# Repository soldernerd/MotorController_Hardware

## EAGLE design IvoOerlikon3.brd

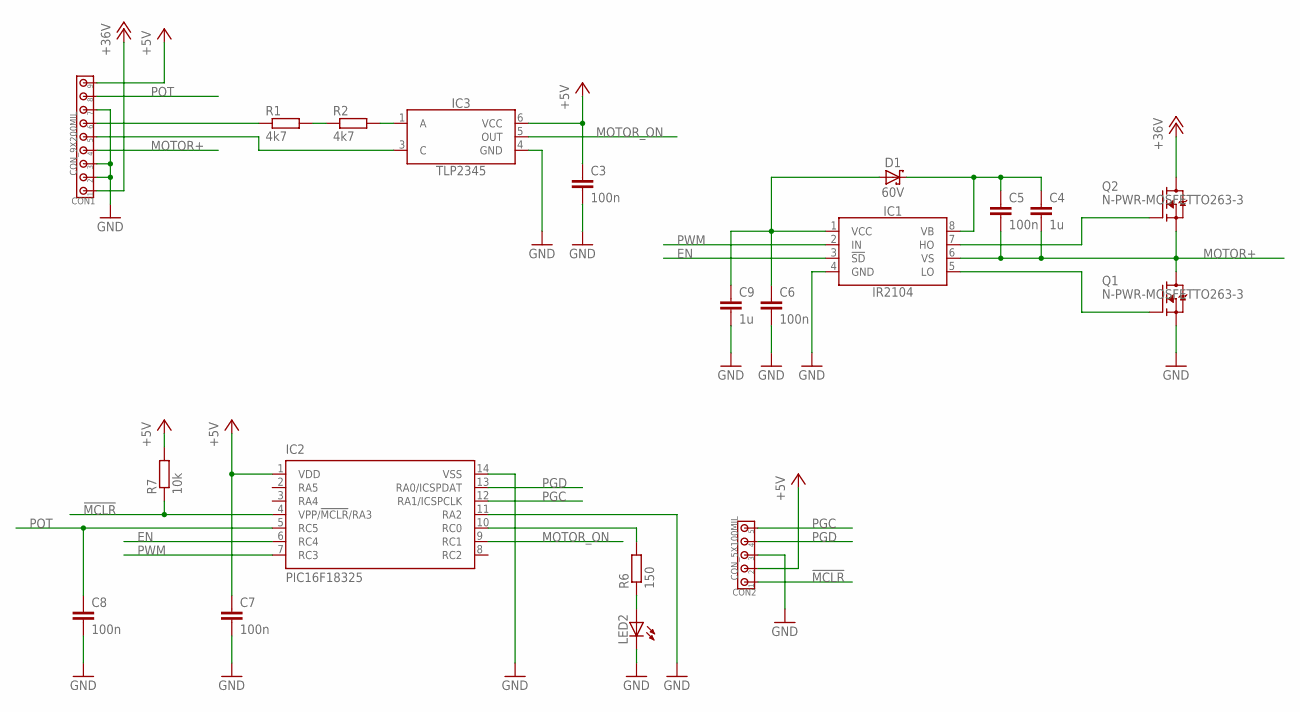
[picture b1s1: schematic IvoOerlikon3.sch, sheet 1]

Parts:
C3, C5, C6, C7, C8: 100n; C0805
C4, C9: 1u; C0805
CON1: CON_9X200MIL; 200MIL_9X
CON2: CON_5X100MIL; 100MIL_5X
D1: 60V; SOD123
IC1: IR2104; SOIC8
IC2: PIC16F18325; SO14
IC3: TLP2345; SO6
LED2: LED0805
Q1, Q2: N-PWR-MOSFETTO263-3; TO263-3
R1, R2: 4k7; R1206
R6: 150; R0805
R7: 10k; R0805

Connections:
!MCLR!: CON2.1, IC2.4 (VPP/!MCLR!/RA3), R7.1
+5V: C3.1, C7.1, CON1.9, CON2.2, IC2.1 (VDD), IC3.6 (VCC), R7.2; also elsewhere on the board
+36V: CON1.1, Q2.TAB (D); also elsewhere on the board
EN: IC1.3 (!SD!), IC2.6 (RC4)
GND: C3.2, C6.2, C7.2, C8.2, C9.2, CON1.2, CON1.3, CON1.7, CON2.3, IC1.4 (GND), IC2.11 (RA2), IC2.14 (VSS), IC3.4 (GND), LED2.C, Q1.3 (S); also elsewhere on the board
MOTOR+: C4.2, C5.2, CON1.4, IC1.6 (VS), Q1.TAB (D), Q2.3 (S)
MOTOR_ON: IC2.9 (RC1), IC3.5 (OUT)
unnamed: R1.2, R2.1
unnamed: IC1.5 (LO), Q1.1 (G)
unnamed: IC3.1 (A), R2.2
unnamed: IC1.7 (HO), Q2.1 (G)
unnamed: C4.1, C5.1, D1.C, IC1.8 (VB)
unnamed: LED2.A, R6.1
unnamed: IC2.10 (RC0), R6.2
unnamed: CON1.6, R1.1
unnamed: CON1.5, IC3.3 (C)
unnamed: C6.1, C9.1, D1.A, IC1.1 (VCC)
PGC: CON2.5, IC2.12 (RA1/ICSPCLK)
PGD: CON2.4, IC2.13 (RA0/ICSPDAT)
POT: C8.1, CON1.8, IC2.5 (RC5)
PWM: IC1.2 (IN), IC2.7 (RC3)

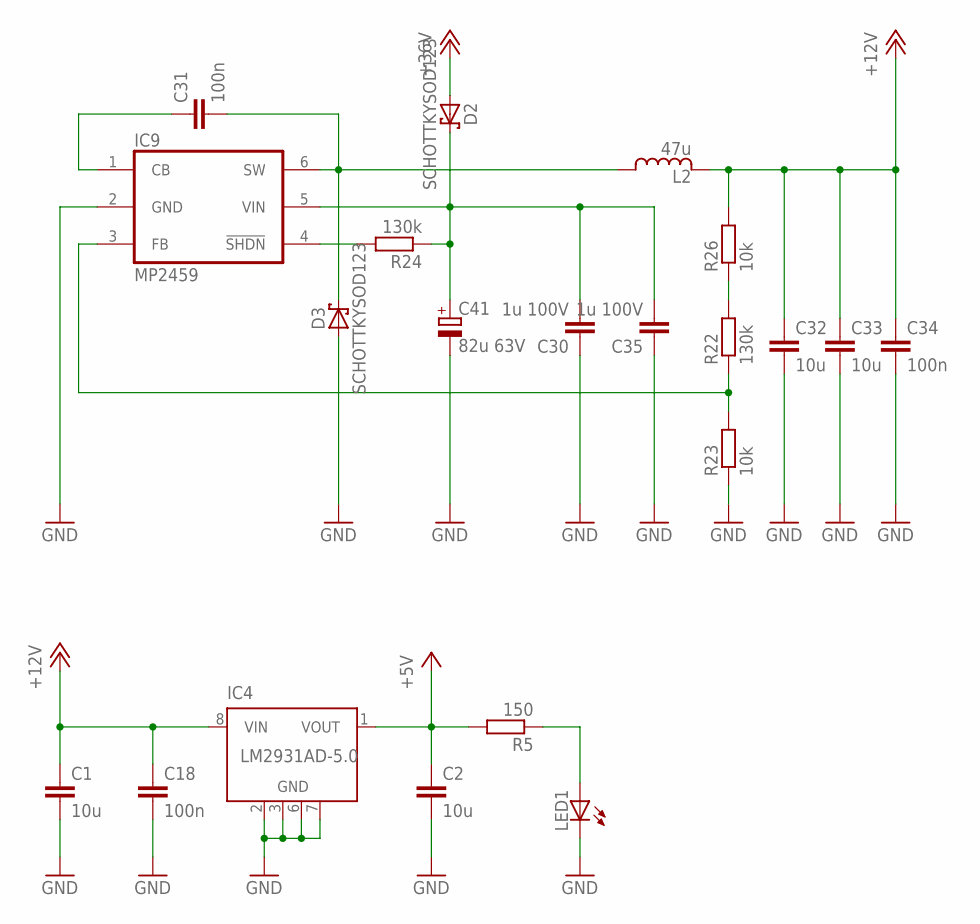
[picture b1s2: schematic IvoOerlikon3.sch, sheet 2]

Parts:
C1, C2, C32, C33: 10u; C1206
C18, C31, C34: 100n; C0805
C30, C35: 1u 100V; C0805
C41: 82u 63V; 8MM
D2, D3: SCHOTTKYSOD123; SOD123
IC4: LM2931AD-5.0; SOIC8
IC9: MP2459; SOT-32-6
L2: 47u; SRN5040
LED1: LED0805
R5: 150; R0805
R22, R24: 130k; R0805
R23, R26: 10k; R0805

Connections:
+5V: C2.1, IC4.1 (VOUT), R5.2; also elsewhere on the board
+12V: C1.1, C18.1, C32.1, C33.1, C34.1, IC4.8 (VIN), L2.2, R26.2
+36V: D2.A; also elsewhere on the board
GND: C1.2, C2.2, C18.2, C30.1, C32.2, C33.2, C34.2, C35.1, C41.-, D3.A, IC4.2 (GND), IC4.3 (GND), IC4.6 (GND), IC4.7 (GND), IC9.2 (GND), LED1.C, R23.1; also elsewhere on the board
unnamed: LED1.A, R5.1
unnamed: IC9.4 (!SHDN!), R24.2
unnamed: C31.1, IC9.1 (CB)
unnamed: IC9.3 (FB), R22.1, R23.2
unnamed: R22.2, R26.1
SWITCH1: C31.2, D3.C, IC9.6 (SW), L2.1
VIN: C30.2, C35.2, C41.+, D2.C, IC9.5 (VIN), R24.1

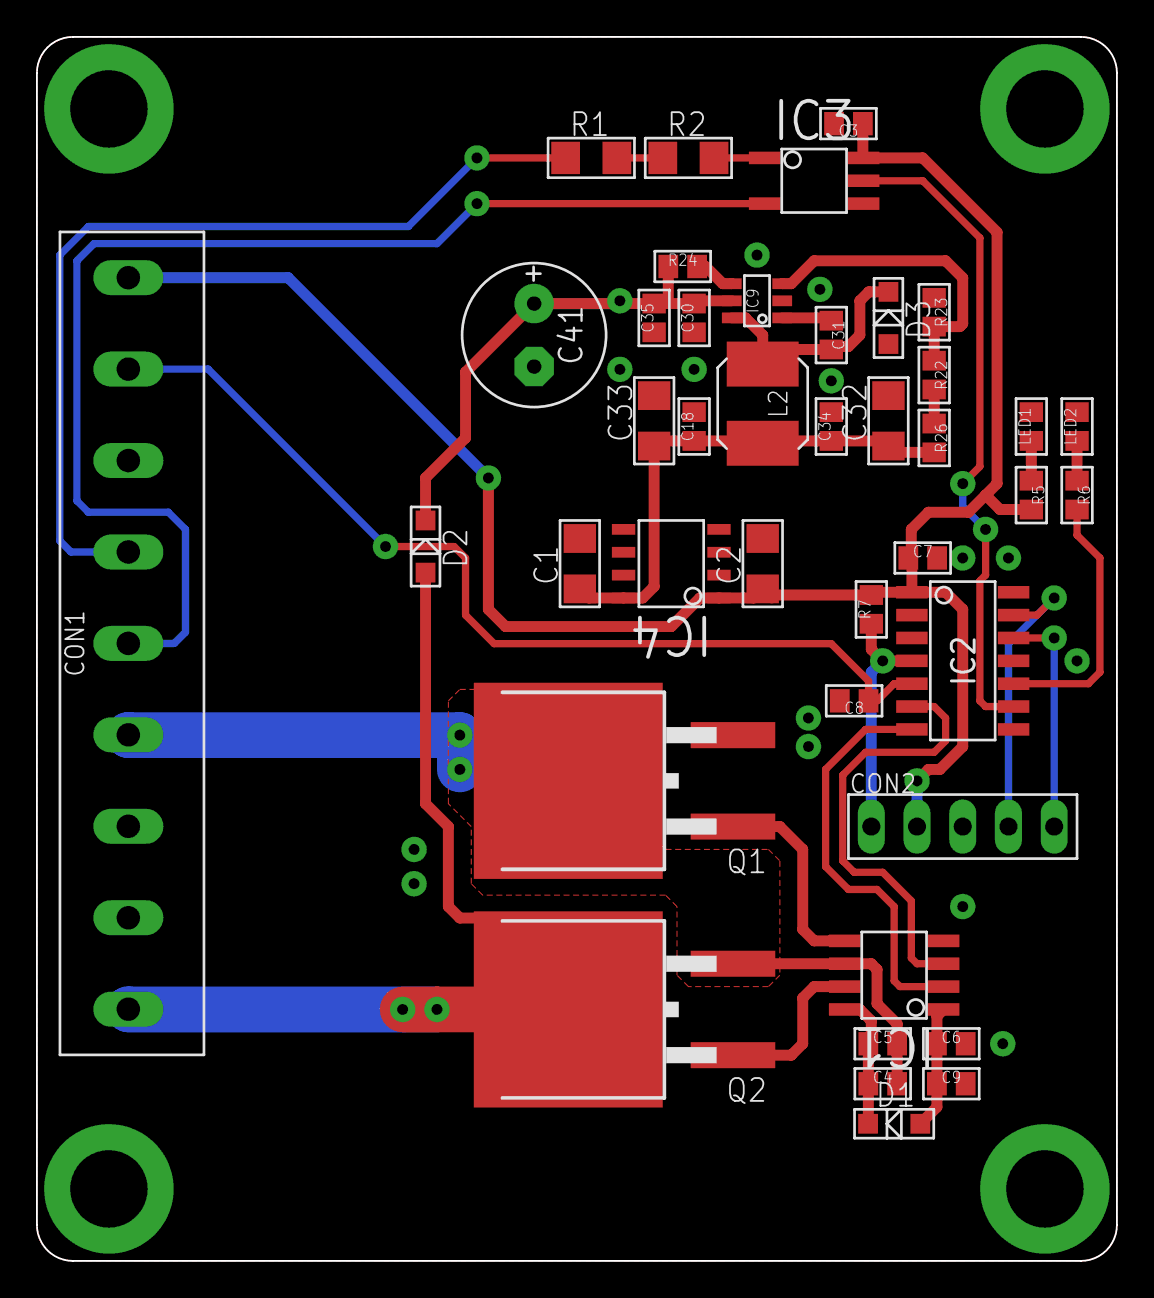
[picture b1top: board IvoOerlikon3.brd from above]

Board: 2 copper layers, 60.0 x 68.0 mm, 41 parts (0 on the bottom side), 29 nets.

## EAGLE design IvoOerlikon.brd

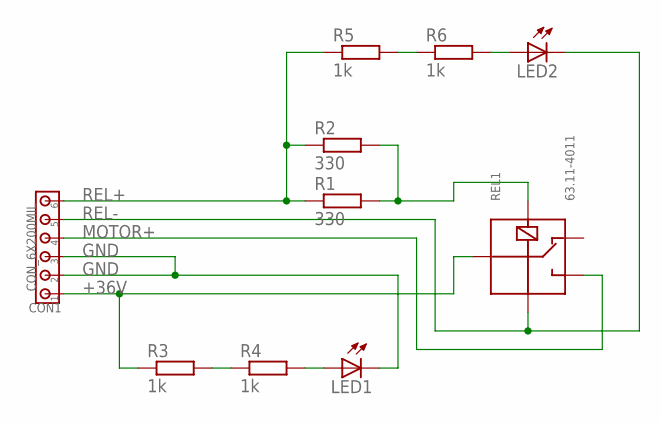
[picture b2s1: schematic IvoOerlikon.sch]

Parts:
CON1: CON_6X200MIL; 200MIL_6X
LED1, LED2: LED1206
R1, R2: 330; R1206
R3, R4, R5, R6: 1k; R1206
REL1: 63.11-4011; G5LE

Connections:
+36V: CON1.1, R3.1, REL1.COM
GND: CON1.2, CON1.3, LED1.C
MOTOR+: CON1.4, REL1.C
unnamed: R1.2, R2.2, REL1.2
unnamed: LED1.A, R4.2
unnamed: R3.2, R4.1
unnamed: LED2.A, R6.2
unnamed: R5.2, R6.1
REL+: CON1.6, R1.1, R2.1, R5.1
REL-: CON1.5, LED2.C, REL1.1

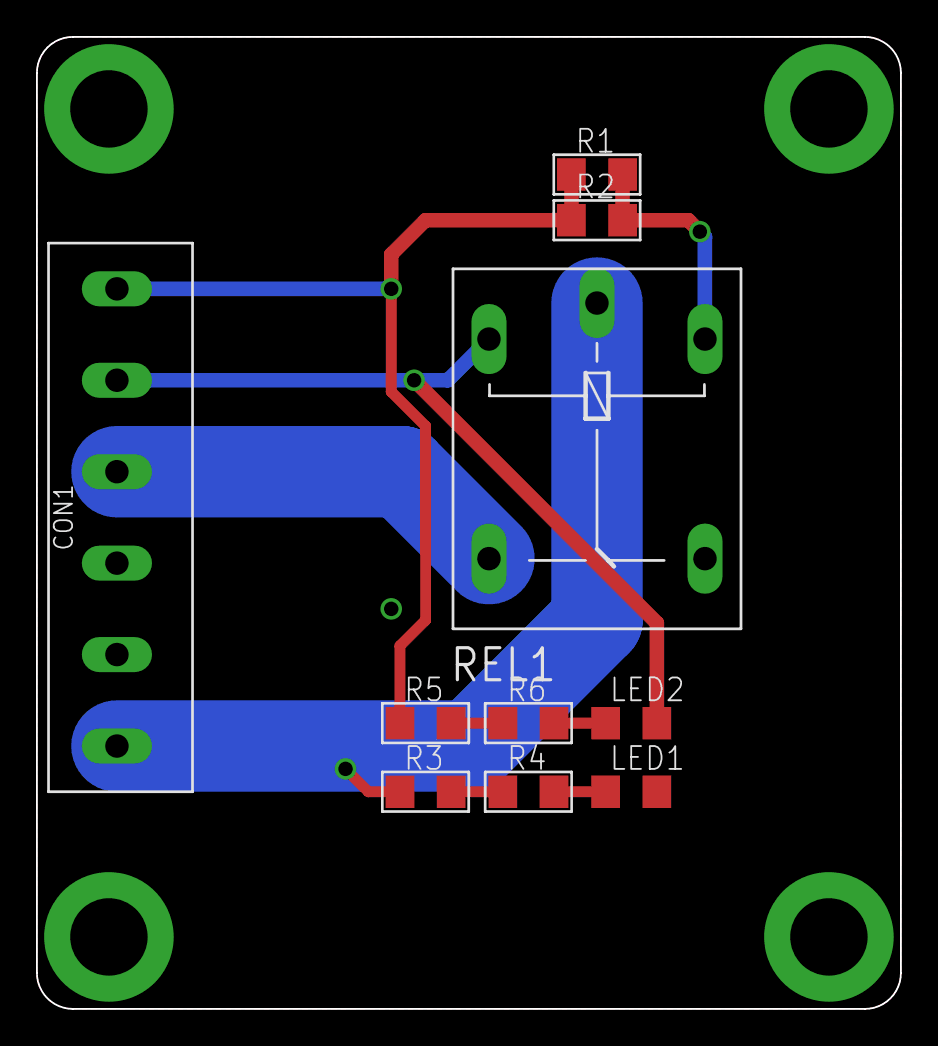
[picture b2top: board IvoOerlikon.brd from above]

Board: 2 copper layers, 48.0 x 54.0 mm, 10 parts (0 on the bottom side), 10 nets.

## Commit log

2023-02-19 Intial commit but already version 3. Now with optocoupler input and 55V capable
